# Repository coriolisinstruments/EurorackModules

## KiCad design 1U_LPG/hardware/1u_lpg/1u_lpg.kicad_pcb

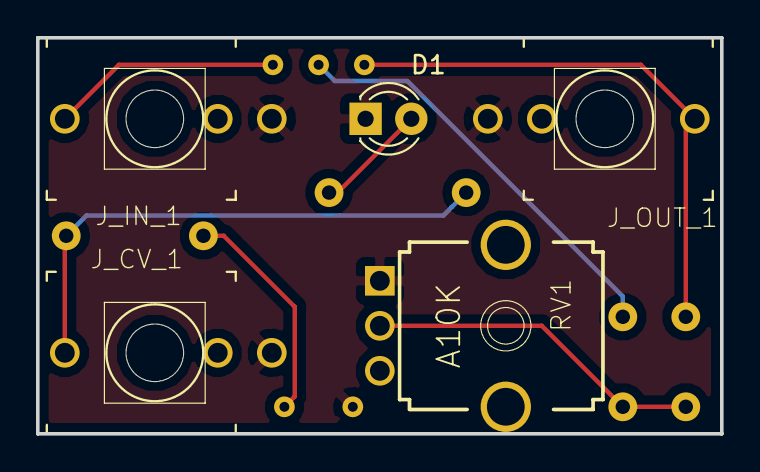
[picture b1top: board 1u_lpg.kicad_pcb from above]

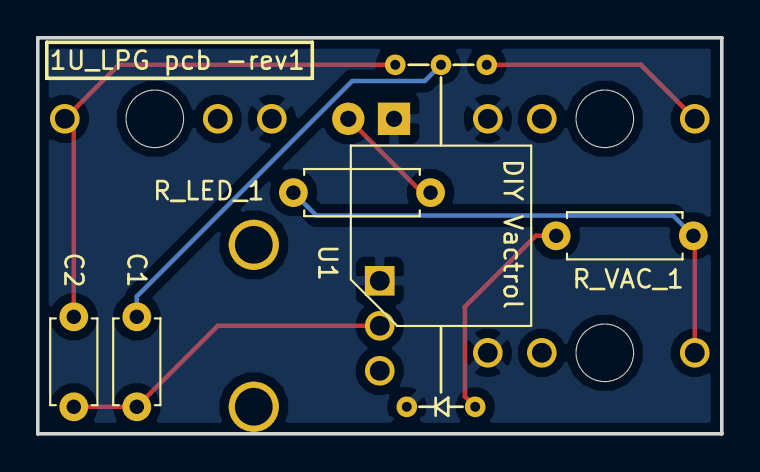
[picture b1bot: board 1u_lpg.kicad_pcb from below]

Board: 2 copper layers, 38.0 x 22.0 mm, 10 parts (5 on the bottom side), 8 nets.

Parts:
C1, C2: 0.1uF; C_Disc_D4.7mm_W2.5mm_P5.00mm
D1: LED; LED_D3.0mm
J_CV_1: thonkiconn; MusicThingModular-WQP-PJ301M-12_JACK
J_IN_1: thonkiconn; MusicThingModular-WQP-PJ301M-12_JACK
J_OUT_1: thonkiconn; MusicThingModular-WQP-PJ301M-12_JACK
RV1: A10K; MusicThingModular-9MM_SNAP-IN_POT
R_LED_1: 20K; R_Axial_DIN0207_L6.3mm_D2.5mm_P7.62mm_Horizontal
R_VAC_1: 100K; R_Axial_DIN0207_L6.3mm_D2.5mm_P7.62mm_Horizontal
U1: VTL5Cx2; DIY_Optoisolator_VTL5Cx2

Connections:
GND: D1.1, J_CV_1.P$3_SLEEVE, J_IN_1.P$3_SLEEVE, J_OUT_1.P$3_SLEEVE, RV1.1, U1.1
unnamed: C1.1, U1.4
unnamed: C1.2, C2.2, RV1.2
unnamed: C2.1, J_OUT_1.P$1_TIP, U1.3
unnamed: D1.2, R_LED_1.1
unnamed: J_CV_1.P$1_TIP, R_LED_1.2, R_VAC_1.2
unnamed: J_IN_1.P$1_TIP, U1.5
unnamed: R_VAC_1.1, U1.2

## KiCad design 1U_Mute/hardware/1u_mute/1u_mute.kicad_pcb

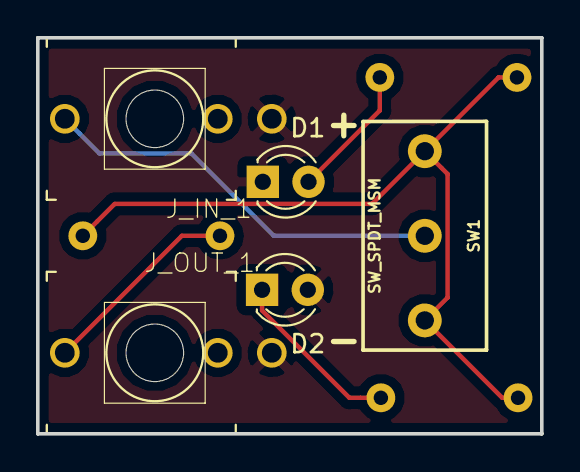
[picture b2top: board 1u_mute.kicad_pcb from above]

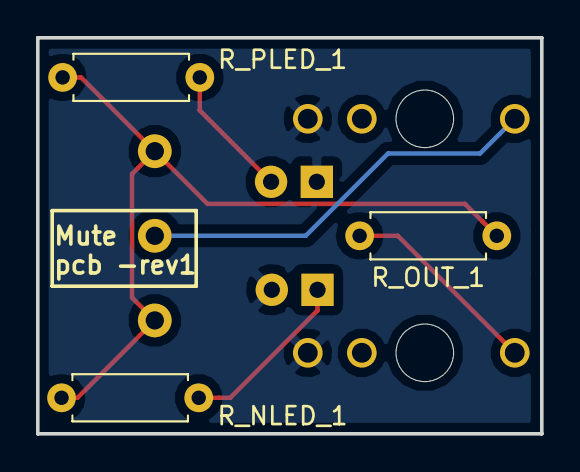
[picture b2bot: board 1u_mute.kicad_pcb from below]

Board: 2 copper layers, 28.0 x 22.0 mm, 8 parts (3 on the bottom side), 6 nets.

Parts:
D1: LED_POS; LED_D3.0mm
D2: LED_NEG; LED_D3.0mm
J_IN_1: thonkiconn; MusicThingModular-WQP-PJ301M-12_JACK
J_OUT_1: thonkiconn; MusicThingModular-WQP-PJ301M-12_JACK
R_NLED_1: 1K; R_Axial_DIN0207_L6.3mm_D2.5mm_P7.62mm_Horizontal
R_OUT_1: 1K; R_Axial_DIN0207_L6.3mm_D2.5mm_P7.62mm_Horizontal
R_PLED_1: 1K; R_Axial_DIN0207_L6.3mm_D2.5mm_P7.62mm_Horizontal
SW1: SW_SPDT_MSM; Miniswitch(4.7mm)

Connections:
GND: D1.1, D2.2, J_IN_1.P$3_SLEEVE, J_OUT_1.P$3_SLEEVE
unnamed: D1.2, R_PLED_1.1
unnamed: D2.1, R_NLED_1.1
unnamed: J_IN_1.P$1_TIP, SW1.2
unnamed: J_OUT_1.P$1_TIP, R_OUT_1.2
unnamed: R_NLED_1.2, R_OUT_1.1, R_PLED_1.2, SW1.1, SW1.3

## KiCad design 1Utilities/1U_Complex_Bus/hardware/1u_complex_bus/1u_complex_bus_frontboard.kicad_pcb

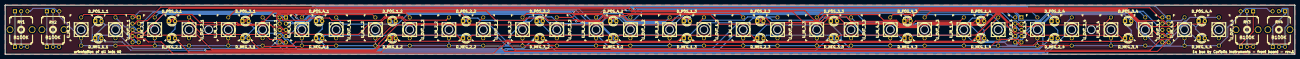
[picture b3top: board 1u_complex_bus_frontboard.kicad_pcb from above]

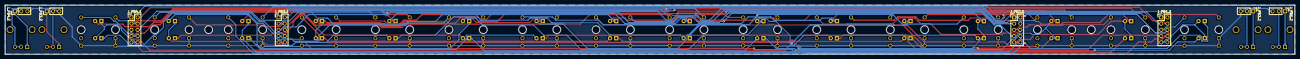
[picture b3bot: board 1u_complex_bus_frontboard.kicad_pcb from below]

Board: 2 copper layers, 526.0 x 20.0 mm, 78 parts (8 on the bottom side), 73 nets.

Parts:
D_NEG_1_1, D_NEG_1_2, D_NEG_1_3, D_NEG_1_4, D_NEG_2_1, D_NEG_2_2, D_NEG_2_3, D_NEG_2_4, D_NEG_3_1, D_NEG_3_2, D_NEG_3_3, D_NEG_3_4, D_NEG_4_1, D_NEG_4_2, D_NEG_4_3, D_NEG_4_4: LED; LED_D3.0mm
D_POS_1_1, D_POS_1_2, D_POS_1_3, D_POS_1_4, D_POS_2_1, D_POS_2_2, D_POS_2_3, D_POS_2_4, D_POS_3_1, D_POS_3_2, D_POS_3_3, D_POS_3_4, D_POS_4_1, D_POS_4_2, D_POS_4_3, D_POS_4_4: LED; LED_D3.0mm
H_FB_1, H_FB_2: MountingHole; MountingHole_3.2mm_M3
J_FB1.1, J_FB2.1, J_FB3.1, J_FB4.1: Conn_02x05_Odd_Even; PinHeader_2x05_P2.54mm_Vertical
J_FB1.2, J_FB2.2, J_FB3.2, J_FB4.2: Conn_01x03; PinHeader_1x03_P2.54mm_Vertical
RV1, RV2, RV3, RV4: B100K; 9MM_SNAP-IN_POT
U_IN_1_1, U_IN_1_2, U_IN_1_3, U_IN_1_4, U_IN_2_1, U_IN_2_2, U_IN_2_3, U_IN_2_4, U_IN_3_1, U_IN_3_2, U_IN_3_3, U_IN_3_4, U_IN_4_1, U_IN_4_2, U_IN_4_3, U_IN_4_4: THONKICONNNEW; MusicThingModular-WQP-PJ301M-12_JACK
U_OUT_1_1, U_OUT_1_2, U_OUT_1_3, U_OUT_1_4, U_OUT_2_1, U_OUT_2_2, U_OUT_2_3, U_OUT_2_4, U_OUT_3_1, U_OUT_3_2, U_OUT_3_3, U_OUT_3_4, U_OUT_4_1, U_OUT_4_2, U_OUT_4_3, U_OUT_4_4: THONKICONNNEW; MusicThingModular-WQP-PJ301M-12_JACK

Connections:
/cv_bus1/FB_IN_1_1: J_FB1.1.1, U_IN_1_1.P$1_TIP
/cv_bus1/FB_IN_1_2: J_FB1.1.2, U_IN_1_2.P$1_TIP
/cv_bus1/FB_IN_1_3: J_FB1.1.3, U_IN_1_3.P$1_TIP
/cv_bus1/FB_IN_1_4: J_FB1.1.4, U_IN_1_4.P$1_TIP
/cv_bus1/FB_LEDS_IN_1: D_NEG_1_1.1, D_POS_1_1.2, J_FB1.1.9
/cv_bus1/FB_LEDS_OUT_1: D_NEG_1_4.2, D_POS_1_4.1, J_FB1.1.10
/cv_bus1/FB_OUT_1_1: J_FB1.1.5, U_OUT_1_1.P$1_TIP
/cv_bus1/FB_OUT_1_2: J_FB1.1.6, U_OUT_1_2.P$1_TIP
/cv_bus1/FB_OUT_1_3: J_FB1.1.7, U_OUT_1_3.P$1_TIP
/cv_bus1/FB_OUT_1_4: J_FB1.1.8, U_OUT_1_4.P$1_TIP
/cv_bus1/FB_POT_1: J_FB1.2.1, RV1.1
/cv_bus1/FB_POT_2: J_FB1.2.2, RV1.2, RV1.3
/cv_bus2/FB_IN_2_1: J_FB2.1.1, U_IN_2_1.P$1_TIP
/cv_bus2/FB_IN_2_2: J_FB2.1.2, U_IN_2_2.P$1_TIP
/cv_bus2/FB_IN_2_3: J_FB2.1.3, U_IN_2_3.P$1_TIP
/cv_bus2/FB_IN_2_4: J_FB2.1.4, U_IN_2_4.P$1_TIP
/cv_bus2/FB_LEDS_IN_2: D_NEG_2_1.1, D_POS_2_1.2, J_FB2.1.9
/cv_bus2/FB_LEDS_OUT_2: D_NEG_2_4.2, D_POS_2_4.1, J_FB2.1.10
/cv_bus2/FB_OUT_2_1: J_FB2.1.5, U_OUT_2_1.P$1_TIP
/cv_bus2/FB_OUT_2_2: J_FB2.1.6, U_OUT_2_2.P$1_TIP
/cv_bus2/FB_OUT_2_3: J_FB2.1.7, U_OUT_2_3.P$1_TIP
/cv_bus2/FB_OUT_2_4: J_FB2.1.8, U_OUT_2_4.P$1_TIP
/cv_bus2/FB_POT_1: J_FB2.2.1, RV2.1
/cv_bus2/FB_POT_2: J_FB2.2.2, RV2.2, RV2.3
/cv_bus3/FB_IN_3_1: J_FB3.1.1, U_IN_3_1.P$1_TIP
/cv_bus3/FB_IN_3_2: J_FB3.1.2, U_IN_3_2.P$1_TIP
/cv_bus3/FB_IN_3_3: J_FB3.1.3, U_IN_3_3.P$1_TIP
/cv_bus3/FB_IN_3_4: J_FB3.1.4, U_IN_3_4.P$1_TIP
/cv_bus3/FB_LEDS_IN_3: D_NEG_3_1.1, D_POS_3_1.2, J_FB3.1.9
/cv_bus3/FB_LEDS_OUT_3: D_NEG_3_4.2, D_POS_3_4.1, J_FB3.1.10
/cv_bus3/FB_OUT_3_1: J_FB3.1.5, U_OUT_3_1.P$1_TIP
/cv_bus3/FB_OUT_3_2: J_FB3.1.6, U_OUT_3_2.P$1_TIP
/cv_bus3/FB_OUT_3_3: J_FB3.1.7, U_OUT_3_3.P$1_TIP
/cv_bus3/FB_OUT_3_4: J_FB3.1.8, U_OUT_3_4.P$1_TIP
/cv_bus3/FB_POT_1: J_FB3.2.1, RV3.1
/cv_bus3/FB_POT_2: J_FB3.2.2, RV3.2, RV3.3
/cv_bus4/FB_IN_4_1: J_FB4.1.1, U_IN_4_1.P$1_TIP
/cv_bus4/FB_IN_4_2: J_FB4.1.2, U_IN_4_2.P$1_TIP
/cv_bus4/FB_IN_4_3: J_FB4.1.3, U_IN_4_3.P$1_TIP
/cv_bus4/FB_IN_4_4: J_FB4.1.4, U_IN_4_4.P$1_TIP
/cv_bus4/FB_LEDS_IN_4: D_NEG_4_1.1, D_POS_4_1.2, J_FB4.1.9
/cv_bus4/FB_LEDS_OUT_4: D_NEG_4_4.2, D_POS_4_4.1, J_FB4.1.10
/cv_bus4/FB_OUT_4_1: J_FB4.1.5, U_OUT_4_1.P$1_TIP
/cv_bus4/FB_OUT_4_2: J_FB4.1.6, U_OUT_4_2.P$1_TIP
/cv_bus4/FB_OUT_4_3: J_FB4.1.7, U_OUT_4_3.P$1_TIP
/cv_bus4/FB_OUT_4_4: J_FB4.1.8, U_OUT_4_4.P$1_TIP
/cv_bus4/FB_POT_1: J_FB4.2.1, RV4.1
/cv_bus4/FB_POT_2: J_FB4.2.2, RV4.2, RV4.3
FB_GND: J_FB1.2.3, J_FB2.2.3, J_FB3.2.3, J_FB4.2.3, U_IN_1_1.P$2_SWITCH, U_IN_1_1.P$3_SLEEVE, U_IN_1_2.P$2_SWITCH, U_IN_1_2.P$3_SLEEVE, U_IN_1_3.P$2_SWITCH, U_IN_1_3.P$3_SLEEVE, U_IN_1_4.P$2_SWITCH, U_IN_1_4.P$3_SLEEVE, U_IN_2_1.P$2_SWITCH, U_IN_2_1.P$3_SLEEVE, U_IN_2_2.P$2_SWITCH, U_IN_2_2.P$3_SLEEVE, U_IN_2_3.P$2_SWITCH, U_IN_2_3.P$3_SLEEVE, U_IN_2_4.P$2_SWITCH, U_IN_2_4.P$3_SLEEVE, U_IN_3_1.P$2_SWITCH, U_IN_3_1.P$3_SLEEVE, U_IN_3_2.P$2_SWITCH, U_IN_3_2.P$3_SLEEVE, U_IN_3_3.P$2_SWITCH, U_IN_3_3.P$3_SLEEVE, U_IN_3_4.P$2_SWITCH, U_IN_3_4.P$3_SLEEVE, U_IN_4_1.P$2_SWITCH, U_IN_4_1.P$3_SLEEVE, U_IN_4_2.P$2_SWITCH, U_IN_4_2.P$3_SLEEVE, U_IN_4_3.P$2_SWITCH, U_IN_4_3.P$3_SLEEVE, U_IN_4_4.P$2_SWITCH, U_IN_4_4.P$3_SLEEVE, U_OUT_1_1.P$3_SLEEVE, U_OUT_1_2.P$3_SLEEVE, U_OUT_1_3.P$3_SLEEVE, U_OUT_1_4.P$3_SLEEVE, U_OUT_2_1.P$3_SLEEVE, U_OUT_2_2.P$3_SLEEVE, U_OUT_2_3.P$3_SLEEVE, U_OUT_2_4.P$3_SLEEVE, U_OUT_3_1.P$3_SLEEVE, U_OUT_3_2.P$3_SLEEVE, U_OUT_3_3.P$3_SLEEVE, U_OUT_3_4.P$3_SLEEVE, U_OUT_4_1.P$3_SLEEVE, U_OUT_4_2.P$3_SLEEVE, U_OUT_4_3.P$3_SLEEVE, U_OUT_4_4.P$3_SLEEVE
unnamed: D_NEG_1_1.2, D_NEG_1_2.1
unnamed: D_NEG_1_2.2, D_NEG_1_3.1
unnamed: D_NEG_1_3.2, D_NEG_1_4.1
unnamed: D_NEG_2_1.2, D_NEG_2_2.1
unnamed: D_NEG_2_2.2, D_NEG_2_3.1
unnamed: D_NEG_2_3.2, D_NEG_2_4.1
unnamed: D_NEG_3_1.2, D_NEG_3_2.1
unnamed: D_NEG_3_2.2, D_NEG_3_3.1
unnamed: D_NEG_3_3.2, D_NEG_3_4.1
unnamed: D_NEG_4_1.2, D_NEG_4_2.1
unnamed: D_NEG_4_2.2, D_NEG_4_3.1
unnamed: D_NEG_4_3.2, D_NEG_4_4.1
unnamed: D_POS_1_1.1, D_POS_1_2.2
unnamed: D_POS_1_2.1, D_POS_1_3.2
unnamed: D_POS_1_3.1, D_POS_1_4.2
unnamed: D_POS_2_1.1, D_POS_2_2.2
unnamed: D_POS_2_2.1, D_POS_2_3.2
unnamed: D_POS_2_3.1, D_POS_2_4.2
unnamed: D_POS_3_1.1, D_POS_3_2.2
unnamed: D_POS_3_2.1, D_POS_3_3.2
unnamed: D_POS_3_3.1, D_POS_3_4.2
unnamed: D_POS_4_1.1, D_POS_4_2.2
unnamed: D_POS_4_2.1, D_POS_4_3.2
unnamed: D_POS_4_3.1, D_POS_4_4.2

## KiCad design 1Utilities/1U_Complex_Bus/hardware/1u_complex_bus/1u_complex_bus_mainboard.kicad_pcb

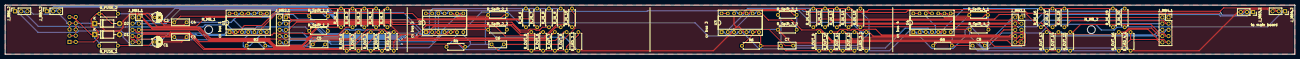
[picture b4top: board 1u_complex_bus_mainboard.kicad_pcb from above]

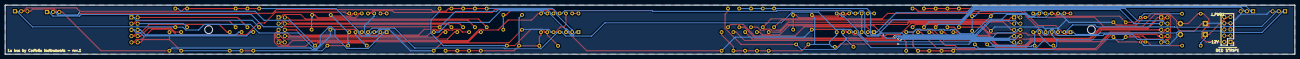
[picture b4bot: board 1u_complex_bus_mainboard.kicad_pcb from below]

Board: 2 copper layers, 526.0 x 20.0 mm, 80 parts (2 on the bottom side), 66 nets.

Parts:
C1, C2: 10uF (25V); CP_Radial_D4.0mm_P2.00mm
C3, C4: 100nF; C_Disc_D7.0mm_W2.5mm_P5.00mm
C5, C6, C7, C8: 10pF; C_Disc_D7.0mm_W2.5mm_P5.00mm
D1, D2: IN4001; D_DO-41_SOD81_P10.16mm_Horizontal
H_MB_1, H_MB_2: MountingHole; MountingHole_3.2mm_M3
J_MB1.1, J_MB2.1, J_MB3.1, J_MB4.1: Conn_02x05_Odd_Even; PinSocket_2x05_P2.54mm_Vertical
J_MB1.2, J_MB2.2, J_MB3.2, J_MB4.2: Conn_01x03; PinSocket_1x03_P2.54mm_Vertical
J_PWR1: Conn_02x05_Odd_Even; PinHeader_2x05_P2.54mm_Vertical
MK1: CoriolisLogo; art_Coriolis_logo_copper
R2, R4, R6, R8: 100K; R_Axial_DIN0207_L6.3mm_D2.5mm_P7.62mm_Horizontal
R_FUSE_1, R_FUSE_2: 10R; R_Axial_DIN0207_L6.3mm_D2.5mm_P7.62mm_Horizontal
R_IN_1, R_IN_2, R_IN_3, R_IN_4, R_IN_5, R_IN_6, R_IN_7, R_IN_8, R_IN_9, R_IN_10, R_IN_11, R_IN_12, R_IN_13, R_IN_14, R_IN_15, R_IN_16, R_IN_17, R_IN_18, R_IN_19, R_IN_20: 100K; R_Axial_DIN0207_L6.3mm_D2.5mm_P7.62mm_Horizontal
R_LED_1_1: 1K; R_Axial_DIN0207_L6.3mm_D2.5mm_P7.62mm_Horizontal
R_LED_2_1: 470R; R_Axial_DIN0207_L6.3mm_D2.5mm_P7.62mm_Horizontal
R_LED_3_1, R_LED_4_1: 5K1; R_Axial_DIN0207_L6.3mm_D2.5mm_P7.62mm_Horizontal
R_OUT_1, R_OUT_2, R_OUT_3, R_OUT_4, R_OUT_5, R_OUT_6, R_OUT_7, R_OUT_8, R_OUT_9, R_OUT_10, R_OUT_11, R_OUT_12, R_OUT_13, R_OUT_14, R_OUT_15, R_OUT_16: 51; R_Axial_DIN0207_L6.3mm_D2.5mm_P7.62mm_Horizontal
R_Split_1_1, R_Split_2_1, R_Split_3_1, R_Split_4_1: 10K; R_Axial_DIN0207_L6.3mm_D2.5mm_P7.62mm_Horizontal
R_Split_1_2, R_Split_2_2, R_Split_3_2, R_Split_4_2: 1K; R_Axial_DIN0207_L6.3mm_D2.5mm_P7.62mm_Horizontal
U1, U2, U3, U4: TL074; DIP-14_W7.62mm_Socket

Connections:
+12V: C1.1, C3.1, R_FUSE_1.1, U1.4, U2.4, U3.4, U4.4
-12V: C2.2, C4.2, R_FUSE_2.1, U1.11, U2.11, U3.11, U4.11
/cv_bus1/IN_1_1: J_MB1.1.1, R_IN_1.1
/cv_bus1/IN_1_2: J_MB1.1.2, R_IN_2.1
/cv_bus1/IN_1_3: J_MB1.1.3, R_IN_3.1
/cv_bus1/IN_1_4: J_MB1.1.4, R_IN_4.1
/cv_bus1/LEDS_IN_1: J_MB1.1.9, U1.8
/cv_bus1/LEDS_OUT_1: C5.1, J_MB1.1.10, R2.2, R_LED_1_1.2, R_OUT_1.1, R_OUT_2.1, R_OUT_3.1, R_OUT_4.1, R_Split_1_1.1, U1.7, U1.9
/cv_bus1/OUT_1_1: J_MB1.1.5, R_OUT_1.2
/cv_bus1/OUT_1_2: J_MB1.1.6, R_OUT_2.2
/cv_bus1/OUT_1_3: J_MB1.1.7, R_OUT_3.2
/cv_bus1/OUT_1_4: J_MB1.1.8, R_OUT_4.2
/cv_bus1/POT_1: J_MB1.2.1, R_IN_5.1, U1.1
/cv_bus1/POT_2: J_MB1.2.2, R_IN_1.2, R_IN_2.2, R_IN_3.2, R_IN_4.2, U1.2
/cv_bus2/IN_2_1: J_MB2.1.1, R_IN_6.1
/cv_bus2/IN_2_2: J_MB2.1.2, R_IN_7.1
/cv_bus2/IN_2_3: J_MB2.1.3, R_IN_8.1
/cv_bus2/IN_2_4: J_MB2.1.4, R_IN_9.1
/cv_bus2/LEDS_IN_2: J_MB2.1.9, U2.8
/cv_bus2/LEDS_OUT_2: C6.1, J_MB2.1.10, R4.2, R_LED_2_1.2, R_OUT_5.1, R_OUT_6.1, R_OUT_7.1, R_OUT_8.1, R_Split_2_1.1, U2.7, U2.9
/cv_bus2/OUT_2_1: J_MB2.1.5, R_OUT_5.2
/cv_bus2/OUT_2_2: J_MB2.1.6, R_OUT_6.2
/cv_bus2/OUT_2_3: J_MB2.1.7, R_OUT_7.2
/cv_bus2/OUT_2_4: J_MB2.1.8, R_OUT_8.2
/cv_bus2/POT_1: J_MB2.2.1, R_IN_10.1, U2.1
/cv_bus2/POT_2: J_MB2.2.2, R_IN_6.2, R_IN_7.2, R_IN_8.2, R_IN_9.2, U2.2
/cv_bus3/IN_3_1: J_MB3.1.1, R_IN_11.1
/cv_bus3/IN_3_2: J_MB3.1.2, R_IN_12.1
/cv_bus3/IN_3_3: J_MB3.1.3, R_IN_13.1
/cv_bus3/IN_3_4: J_MB3.1.4, R_IN_14.1
/cv_bus3/LEDS_IN_3: J_MB3.1.9, U3.8
/cv_bus3/LEDS_OUT_3: J_MB3.1.10, R_LED_3_1.2, U3.9
/cv_bus3/OUT_3_1: J_MB3.1.5, R_OUT_9.2
/cv_bus3/OUT_3_2: J_MB3.1.6, R_OUT_10.2
/cv_bus3/OUT_3_3: J_MB3.1.7, R_OUT_11.2
/cv_bus3/OUT_3_4: J_MB3.1.8, R_OUT_12.2
/cv_bus3/POT_1: J_MB3.2.1, R_IN_15.1, U3.1
/cv_bus3/POT_2: J_MB3.2.2, R_IN_11.2, R_IN_12.2, R_IN_13.2, R_IN_14.2, U3.2
/cv_bus4/IN_4_1: J_MB4.1.1, R_IN_16.1
/cv_bus4/IN_4_2: J_MB4.1.2, R_IN_17.1
/cv_bus4/IN_4_3: J_MB4.1.3, R_IN_18.1
/cv_bus4/IN_4_4: J_MB4.1.4, R_IN_19.1
/cv_bus4/LEDS_IN_4: J_MB4.1.9, U4.8
/cv_bus4/LEDS_OUT_4: C8.1, J_MB4.1.10, R8.2, R_LED_4_1.2, R_OUT_13.1, R_OUT_14.1, R_OUT_15.1, R_OUT_16.1, R_Split_4_1.1, U4.7, U4.9
/cv_bus4/OUT_4_1: J_MB4.1.5, R_OUT_13.2
/cv_bus4/OUT_4_2: J_MB4.1.6, R_OUT_14.2
/cv_bus4/OUT_4_3: J_MB4.1.7, R_OUT_15.2
/cv_bus4/OUT_4_4: J_MB4.1.8, R_OUT_16.2
/cv_bus4/POT_1: J_MB4.2.1, R_IN_20.1, U4.1
/cv_bus4/POT_2: J_MB4.2.2, R_IN_16.2, R_IN_17.2, R_IN_18.2, R_IN_19.2, U4.2
GND: C1.2, C2.1, C3.2, C4.1, D1.2, D2.1, J_MB1.2.3, J_MB2.2.3, J_MB3.2.3, J_MB4.2.3, J_PWR1.3, J_PWR1.4, J_PWR1.5, J_PWR1.6, J_PWR1.7, J_PWR1.8, R_LED_1_1.1, R_LED_2_1.1, R_LED_3_1.1, R_LED_4_1.1, R_Split_1_2.1, R_Split_2_2.1, R_Split_3_2.1, R_Split_4_2.1, U1.3, U1.5, U1.12, U2.3, U2.5, U2.12, U3.3, U3.5, U3.12, U4.3, U4.5, U4.12
unnamed: C5.2, R2.1, R_IN_5.2, U1.6
unnamed: C6.2, R4.1, R_IN_10.2, U2.6
unnamed: C7.1, R6.2, R_OUT_9.1, R_OUT_10.1, R_OUT_11.1, R_OUT_12.1, R_Split_3_1.1, U3.7
unnamed: C7.2, R6.1, R_IN_15.2, U3.6
unnamed: C8.2, R8.1, R_IN_20.2, U4.6
unnamed: D1.1, J_PWR1.9, J_PWR1.10, R_FUSE_1.2
unnamed: D2.2, J_PWR1.1, J_PWR1.2, R_FUSE_2.2
unnamed: R_Split_1_1.2, R_Split_1_2.2, U1.10
unnamed: R_Split_2_1.2, R_Split_2_2.2, U2.10
unnamed: R_Split_3_1.2, R_Split_3_2.2, U3.10
unnamed: R_Split_4_1.2, R_Split_4_2.2, U4.10
unnamed: U1.13, U1.14
unnamed: U2.13, U2.14
unnamed: U3.13, U3.14
unnamed: U4.13, U4.14

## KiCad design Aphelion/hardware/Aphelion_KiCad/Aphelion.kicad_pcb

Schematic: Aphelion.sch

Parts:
C1, C4, C5, C12, C17, C18: 10uF; CP_Radial_D5.0mm_P2.50mm
C2, C6, C9, C16: 220nF; C_Rect_L7.0mm_W2.5mm_P5.00mm
C3, C15, C19, C20, C21, C22: 47nF; C_Rect_L7.0mm_W2.5mm_P5.00mm
C7, C8: 100nF; C_Rect_L7.0mm_W2.5mm_P5.00mm
C10: 1uF; C_Rect_L7.0mm_W2.5mm_P5.00mm
C11, C23, C24: 33uF; CP_Radial_D5.0mm_P2.50mm
C13, C14: 22nF; C_Rect_L7.0mm_W2.5mm_P5.00mm
D1, D2: 1N4001; D_DO-41_SOD81_P10.16mm_Horizontal
F1, F2: Polyfuse; Fuse_TE5_Littlefuse-395Series
J1: Conn_02x05_Odd_Even; Pin_Header_Straight_2x05_Pitch2.54mm
J2: Conn_01x08_Male; Pin_Header_Straight_1x08_Pitch2.54mm
J3, J4: Conn_01x06_Male; Pin_Header_Straight_1x06_Pitch2.54mm
J5: Conn_01x08_Female; Pin_Header_Straight_1x08_Pitch2.54mm
J6, J7: Conn_01x06_Female; Pin_Header_Straight_1x06_Pitch2.54mm
J_IN1: Audio-Jack-2_Switch; WQP-PJ301M-12_JACK
J_OUT1: Audio-Jack-2_Switch; WQP-PJ301M-12_JACK
Q1, Q2, Q3, Q4: BC547; TO-92_Molded_Narrow
R1, R2, R5, R6, R7, R10, R17: 47K; R_Axial_DIN0207_L6.3mm_D2.5mm_P7.62mm_Horizontal
R3, R11, R12, R15, R16, R18, R19, R23, R25: 10K; R_Axial_DIN0207_L6.3mm_D2.5mm_P7.62mm_Horizontal
R4, R26, R27: 1M; R_Axial_DIN0207_L6.3mm_D2.5mm_P7.62mm_Horizontal
R8, R9, R30, R31, R32, R33: 100K; R_Axial_DIN0207_L6.3mm_D2.5mm_P7.62mm_Horizontal
R13: 470r; R_Axial_DIN0207_L6.3mm_D2.5mm_P7.62mm_Horizontal
R14: 20K; R_Axial_DIN0207_L6.3mm_D2.5mm_P7.62mm_Horizontal
R20, R21: 5K6; R_Axial_DIN0207_L6.3mm_D2.5mm_P7.62mm_Horizontal
R22, R24: 22K; R_Axial_DIN0207_L6.3mm_D2.5mm_P7.62mm_Horizontal
R28, R29: 3M9; R_Axial_DIN0207_L6.3mm_D2.5mm_P7.62mm_Horizontal
R34, R35: 4K7; R_Axial_DIN0207_L6.3mm_D2.5mm_P7.62mm_Horizontal
R36, R37, R38, R39: 220K; R_Axial_DIN0207_L6.3mm_D2.5mm_P7.62mm_Horizontal
RV_COMP_H1: A500K; 9MM_SNAP-IN_POT
RV_COMP_L1: A500K; 9MM_SNAP-IN_POT
RV_LVL_H1: A100K; 9MM_SNAP-IN_POT
RV_LVL_L1: A100K; 9MM_SNAP-IN_POT
RV_XOVER_F1: A100K; DUAL_9MM_SNAP-IN_POT
U1: TL072; DIP-8_W7.62mm_Socket
U2, U3: TL074; DIP-14_W7.62mm_Socket
U4, U5: NSL-32; Optoisolator_NSL-32

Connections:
/+6V: C11.1, J5.2, R7.1, R8.2, R9.1, R14.1, R16.1, R18.1, R26.1, R27.1, U1.3 (+), U2.10 (+), U2.12 (+), U3.10 (+), U3.12 (+)
/+6V_FB: J2.2, R4.1, RV_LVL_H1.3, RV_LVL_L1.3
/+12V: C4.1, C7.1, F1.1, R8.1, R34.2, R35.2, U1.8 (V+), U2.4 (V+), U3.4 (V+)
/-12V: C5.2, C8.2, F2.2, U1.4 (V-), U2.11 (V-), U3.11 (V-)
/A_IN: J5.3, U2.3 (+)
/A_IN_FB: J2.3, R3.1, R4.2
/A_OUT: J5.4, R10.1, U1.7
/A_OUT_FB: J2.4, R13.2
/COMP_H_OUT: C3.2, C21.2, R32.1, U3.8
/COMP_L_OUT: C1.1, C22.2, R33.1, U3.14
/GND: C4.2, C5.1, C7.2, C8.1, C11.2, C15.2, C16.2, C23.2, C24.2, D1.2 (A), D2.1 (K), J1.3, J1.4, J1.5, J1.6, J1.7, J1.8, J5.1, Q1.3 (E), Q2.3 (E), Q3.3 (E), Q4.3 (E), R9.2, R36.2, R37.2, R38.1, R39.1
/GND_FB: J2.1, J_IN1.2, J_OUT1.2, R17.1
/RV_COMP_H_1: C15.1, J6.1, J6.2
/RV_COMP_H_1_FB: J3.1, RV_COMP_H1.1
/RV_COMP_H_2_FB: J3.2, RV_COMP_H1.2
/RV_COMP_H_3: J6.3, R22.2
/RV_COMP_H_3_FB: J3.3, RV_COMP_H1.3
/RV_COMP_L_1: C16.1, J6.4, J6.5
/RV_COMP_L_1_FB: J3.4, RV_COMP_L1.1
/RV_COMP_L_2_FB: J3.5, RV_COMP_L1.2
/RV_COMP_L_3: J6.6, R24.2
/RV_COMP_L_3_FB: J3.6, RV_COMP_L1.3
/RV_LVL_H_1: C3.1, J5.7
/RV_LVL_H_1_FB: J2.7, RV_LVL_H1.1
/RV_LVL_H_2: C9.2, J5.8
/RV_LVL_H_2_FB: J2.8, RV_LVL_H1.2
/RV_LVL_L_1: C1.2, J5.5
/RV_LVL_L_1_FB: J2.5, RV_LVL_L1.1
/RV_LVL_L_2: C2.2, J5.6
/RV_LVL_L_2_FB: J2.6, RV_LVL_L1.2
/RV_XOVER_1: C17.1, J7.1, R15.1, U2.7
/RV_XOVER_1_FB: J4.1, RV_XOVER_F1.1
/RV_XOVER_2: J7.2, R20.2
/RV_XOVER_2_FB: J4.2, RV_XOVER_F1.2
/RV_XOVER_3: J7.3, R16.2
/RV_XOVER_3_FB: J4.3, RV_XOVER_F1.3
/RV_XOVER_4: C13.1, J7.4, R14.2, U2.5 (+), U2.8
/RV_XOVER_4_FB: J4.4, RV_XOVER_F1.4
/RV_XOVER_5: J7.5, R21.2
/RV_XOVER_5_FB: J4.5, RV_XOVER_F1.5
/RV_XOVER_6: J7.6, R18.2
/RV_XOVER_6_FB: J4.6, RV_XOVER_F1.6
/X_OVER_L_OUT: C14.1, C18.1, R19.2, U2.14
unnamed: C2.1, R1.2
unnamed: C6.1, R3.2
unnamed: C6.2, J_IN1.1
unnamed: C9.1, R5.2
unnamed: C10.1, R11.2
unnamed: C10.2, U2.1, U2.2 (-)
unnamed: C12.1, R13.1
unnamed: C12.2, J_OUT1.1, R17.2
unnamed: C13.2, R20.1, U2.9 (-)
unnamed: C14.2, R21.1, U2.13 (-)
unnamed: C17.2, R23.2
unnamed: C18.2, R25.2
unnamed: C19.1, Q1.2 (B), R36.1
unnamed: C19.2, R28.1, R30.2, U3.1, U4.4 (R)
unnamed: C20.1, Q2.2 (B), R37.1
unnamed: C20.2, R29.1, R31.2, U3.7, U5.4 (R)
unnamed: C21.1, Q3.2 (B), R38.2
unnamed: C22.1, Q4.2 (B), R39.2
unnamed: C23.1, Q1.1 (C), Q3.1 (C), U4.2 (K)
unnamed: C24.1, Q2.1 (C), Q4.1 (C), U5.2 (K)
unnamed: D1.1 (K), F1.2, J1.9, J1.10
unnamed: D2.2 (A), F2.1, J1.1, J1.2
unnamed: R1.1, R2.2, U1.2 (-)
unnamed: R2.1, R6.2, U1.1
unnamed: R5.1, R7.2, U1.5 (+)
unnamed: R6.1, R10.2, U1.6 (-)
unnamed: R11.1, R12.2
unnamed: R12.1, R15.2, R19.1, U2.6 (-)
unnamed: R22.1, R28.2, U3.2 (-), U4.3 (R)
unnamed: R23.1, R26.2, U3.3 (+)
unnamed: R24.1, R29.2, U3.6 (-), U5.3 (R)
unnamed: R25.1, R27.2, U3.5 (+)
unnamed: R30.1, R32.2, U3.9 (-)
unnamed: R31.1, R33.2, U3.13 (-)
unnamed: R34.1, U4.1 (A)
unnamed: R35.1, U5.1 (A)

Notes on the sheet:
Input from busboard
Voltage divider
Input and cross-over
Output
High Compressor
Low Compressor
Front board

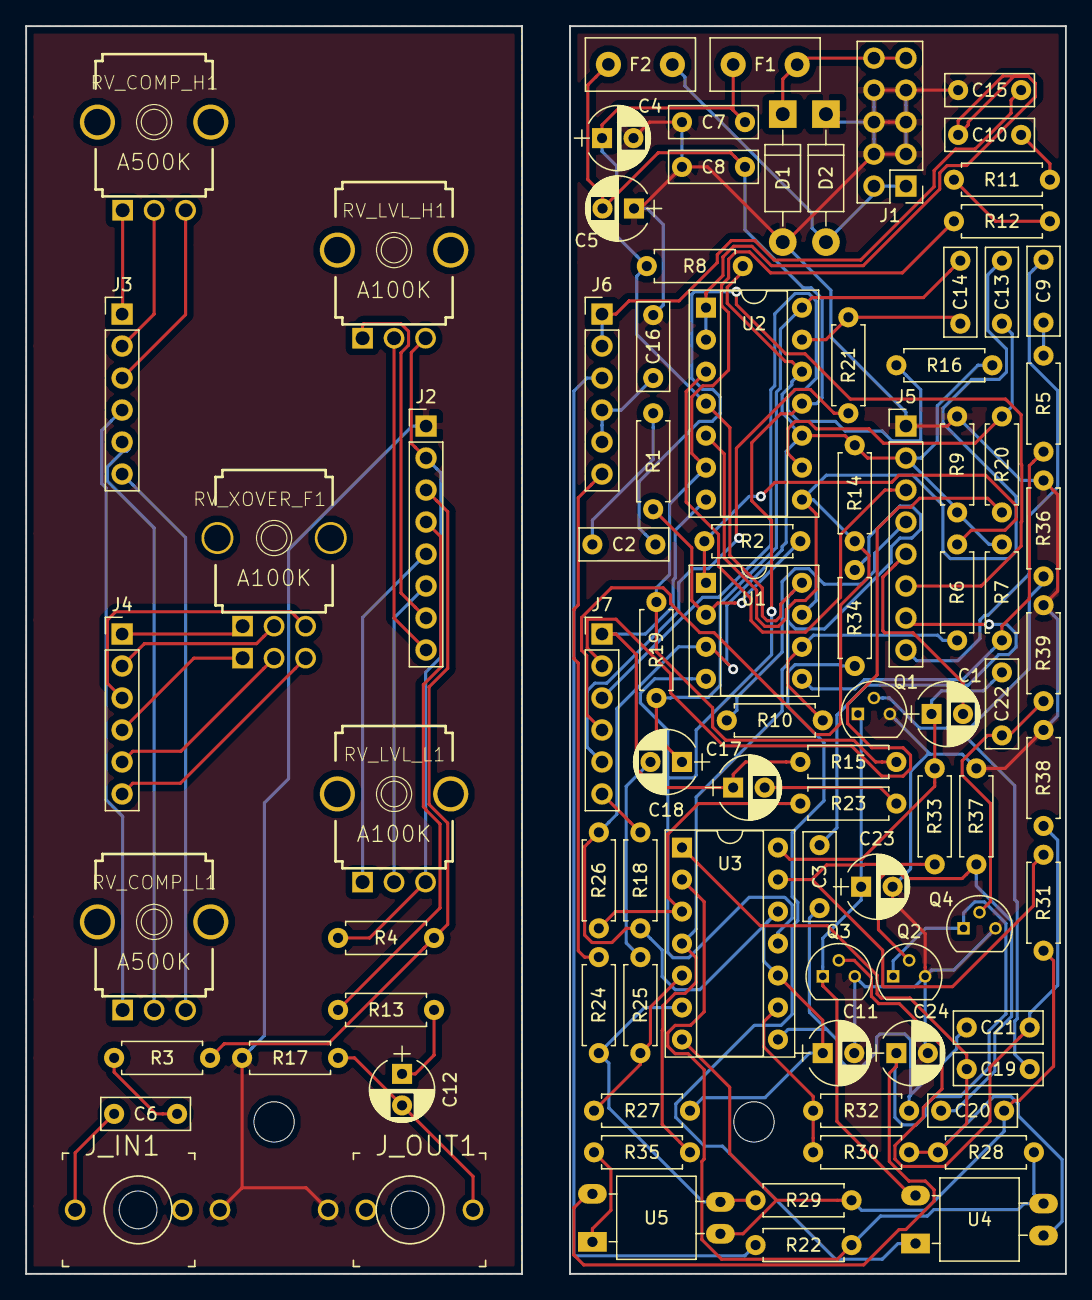
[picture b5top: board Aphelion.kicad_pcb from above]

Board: 2 copper layers, 39.4 x 99.1 mm, 90 parts (0 on the bottom side), 79 nets.

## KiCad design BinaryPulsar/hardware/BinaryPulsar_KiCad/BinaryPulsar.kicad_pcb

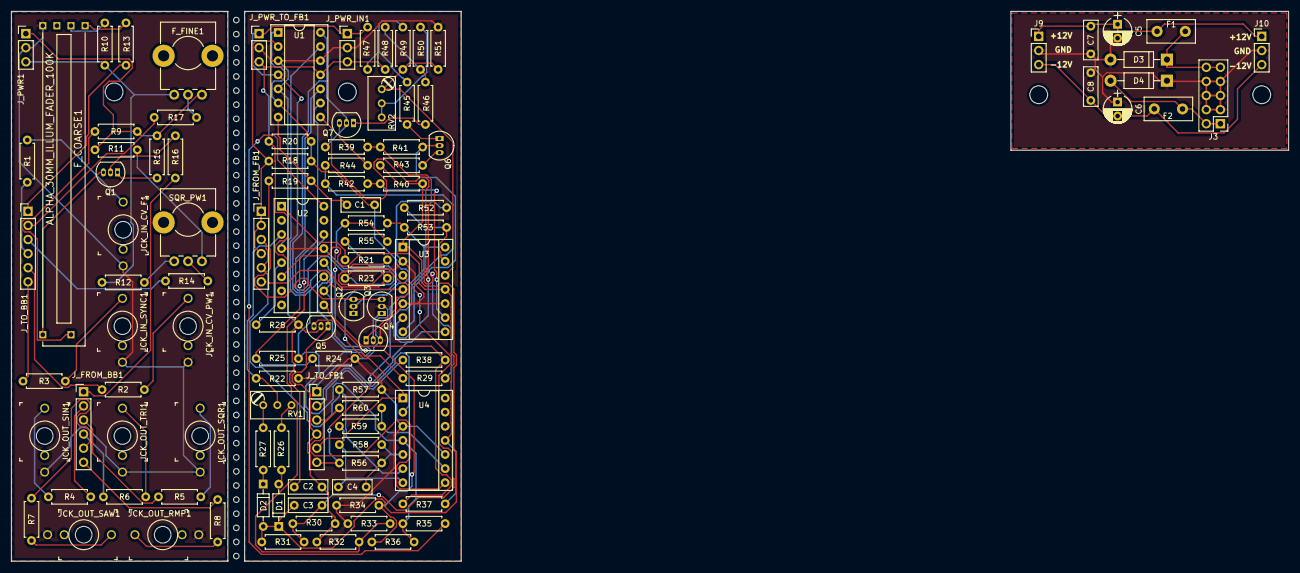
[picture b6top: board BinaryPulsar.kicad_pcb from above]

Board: 2 copper layers, 230.0 x 99.0 mm, 112 parts (0 on the bottom side), 88 nets.

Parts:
C1: 100pF; C_Rect_L7.0mm_W2.5mm_P5.00mm
C2: 0.02uF; C_Rect_L7.0mm_W2.5mm_P5.00mm
C3, C4: 10pF; C_Rect_L7.0mm_W2.5mm_P5.00mm
C5, C6: 10uF; CP_Radial_D5.0mm_P2.50mm
C7, C8: 100nF; C_Rect_L7.0mm_W2.5mm_P5.00mm
D1, D2: 1N4148; D_DO-35_SOD27_P7.62mm_Horizontal
D3, D4: 1N4001; D_DO-41_SOD81_P10.16mm_Horizontal
F1, F2: Polyfuse; Fuse_TE5_Littlefuse-395Series
F_COARSE1: ALPHA_30MM_ILLUM_FADER_100K; ALPHA_ILL_FADER_45MM
F_FINE1: 100K; Potentiometer_Alps_RK09K_Horizontal
J3: Conn_02x05_Odd_Even; Pin_Header_Straight_2x05_Pitch2.54mm
J9, J10: Conn_01x03_Male; Pin_Header_Straight_1x03_Pitch2.54mm
JCK_IN_CV_F1: THONKICONNNEW; WQP-PJ301M-12_JACK
JCK_IN_CV_PW1: THONKICONNNEW; WQP-PJ301M-12_JACK
JCK_IN_SYNC1: THONKICONNNEW; WQP-PJ301M-12_JACK
JCK_OUT_RMP1: THONKICONNNEW; WQP-PJ301M-12_JACK
JCK_OUT_SAW1: THONKICONNNEW; WQP-PJ301M-12_JACK
JCK_OUT_SIN1: THONKICONNNEW; WQP-PJ301M-12_JACK
JCK_OUT_SQR1: THONKICONNNEW; WQP-PJ301M-12_JACK
JCK_OUT_TRI1: THONKICONNNEW; WQP-PJ301M-12_JACK
J_FROM_BB1: Conn_01x06_Male; Pin_Header_Straight_1x06_Pitch2.54mm
J_FROM_FB1: Conn_01x06_Female; Pin_Header_Straight_1x06_Pitch2.54mm
J_PWR1: Conn_01x03_Male; Pin_Header_Straight_1x03_Pitch2.54mm
J_PWR_IN1: Conn_01x03_Male; Pin_Header_Straight_1x03_Pitch2.54mm
J_PWR_TO_FB1: Conn_01x03_Female; Pin_Header_Straight_1x03_Pitch2.54mm
J_TO_BB1: Conn_01x06_Male; Pin_Header_Straight_1x06_Pitch2.54mm
J_TO_FB1: Conn_01x06_Female; Pin_Header_Straight_1x06_Pitch2.54mm
Q1, Q2, Q3: BC547; TO-92_Inline_Narrow_Oval
Q4: BC557; TO-92_Inline_Narrow_Oval
Q5, Q6, Q7: MPF102; TO-92_Inline_Narrow_Oval
R1, R3, R11, R12, R13, R16, R23, R25, R26, R27, R29, R53, R56: 100K; R_Axial_DIN0207_L6.3mm_D2.5mm_P7.62mm_Horizontal
R2, R14, R19, R21, R24, R45, R46, R49, R51, R54, R55, R60: 10K; R_Axial_DIN0207_L6.3mm_D2.5mm_P7.62mm_Horizontal
R4, R5, R6, R7, R8, R22, R38: 1K; R_Axial_DIN0207_L6.3mm_D2.5mm_P7.62mm_Horizontal
R9, R10, R59: 27K; R_Axial_DIN0207_L6.3mm_D2.5mm_P7.62mm_Horizontal
R15, R18, R33: 2K; R_Axial_DIN0207_L6.3mm_D2.5mm_P7.62mm_Horizontal
R17: 3M; R_Axial_DIN0207_L6.3mm_D2.5mm_P7.62mm_Horizontal
R20, R58: 4.7M; R_Axial_DIN0207_L6.3mm_D2.5mm_P7.62mm_Horizontal
R28: 39K; R_Axial_DIN0207_L6.3mm_D2.5mm_P7.62mm_Horizontal
R30: 120K; R_Axial_DIN0207_L6.3mm_D2.5mm_P7.62mm_Horizontal
R31: 270K; R_Axial_DIN0207_L6.3mm_D2.5mm_P7.62mm_Horizontal
R32: 110K; R_Axial_DIN0207_L6.3mm_D2.5mm_P7.62mm_Horizontal
R34: 180K; R_Axial_DIN0207_L6.3mm_D2.5mm_P7.62mm_Horizontal
R35: 680K; R_Axial_DIN0207_L6.3mm_D2.5mm_P7.62mm_Horizontal
R36: 2M; R_Axial_DIN0207_L6.3mm_D2.5mm_P7.62mm_Horizontal
R37: 4.7K; R_Axial_DIN0207_L6.3mm_D2.5mm_P7.62mm_Horizontal
R39, R41: 20K; R_Axial_DIN0207_L6.3mm_D2.5mm_P7.62mm_Horizontal
R40, R42, R52: 47K; R_Axial_DIN0207_L6.3mm_D2.5mm_P7.62mm_Horizontal
R43, R44: 30K; R_Axial_DIN0207_L6.3mm_D2.5mm_P7.62mm_Horizontal
R47, R48: 15K; R_Axial_DIN0207_L6.3mm_D2.5mm_P7.62mm_Horizontal
R50: 9.1K; R_Axial_DIN0207_L6.3mm_D2.5mm_P7.62mm_Horizontal
R57: 1M; R_Axial_DIN0207_L6.3mm_D2.5mm_P7.62mm_Horizontal
RV1: 100K; Potentiometer_Trimmer_Bourns_3296W
RV2: 2K; Potentiometer_Trimmer_Bourns_3296W
SQR_PW1: 100K; Potentiometer_Alps_RK09K_Horizontal
U1, U3, U4: TL074; DIP-14_W7.62mm_Socket
U2: LM13700; DIP-16_W7.62mm_Socket
screw: MountingHole_3.2mm_M3
screw#2, screw#3, screw#4: MountingHole_3.2mm_M3

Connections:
+12V: J_PWR_IN1.1, J_PWR_TO_FB1.1, R25.2, R35.2, R36.2, R47.2, U1.4, U2.11, U3.4, U4.4
/LFO back board/-12V: J_PWR_IN1.3, J_PWR_TO_FB1.3, R20.1, R37.1, R48.1, U1.11, U2.6, U3.11, U4.11
/LFO back board/GND: J_PWR_IN1.2, J_PWR_TO_FB1.2, Q3.2, Q4.3, R22.1, R23.1, R24.1, R33.1, R34.1, R51.1, R52.2, R57.2, U1.3, U1.5, U1.12, U2.4, U2.13, U3.2, U3.5, U3.10, U4.3, U4.10
/LFO back board/Integrator/BIAS_INPUT: R21.1, U2.1
/LFO back board/Integrator/SQR_RAW: C3.1, D1.1, D2.2, R31.1, R40.2, R43.2, U3.1
/LFO back board/LED_RATE: J_TO_FB1.1, R42.1, R44.2, U3.8
/LFO back board/RMP: J_TO_FB1.6, R53.1, R54.2, R56.2, U3.14
/LFO back board/SAW: J_TO_FB1.5, R55.1, U4.1
/LFO back board/SIN: J_TO_FB1.2, R38.1
/LFO back board/SQR: J_TO_FB1.3, R60.1, U4.8
/LFO back board/TRI: C2.1, J_TO_FB1.4, Q5.1, Q7.2, R30.2, R32.2, R39.2, U1.14
/LFO back board/V_CF: J_FROM_FB1.1, J_FROM_FB1.2, J_FROM_FB1.4, R18.2, U1.2
/LFO back board/V_CV_PW: J_FROM_FB1.3, J_FROM_FB1.5, R57.1, U4.6
/LFO back board/V_SYNC: J_FROM_FB1.6, R23.2, U1.10
/LFO front board/+12V_FB: F_FINE1.1, J_PWR1.1, R9.1, R11.2, R15.2
/LFO front board/-12V_FB: F_FINE1.3, J_PWR1.3, R10.2, R12.2
/LFO front board/GND_FB: F_COARSE1.E, JCK_IN_CV_F1.P$3_SLEEVE, JCK_IN_CV_PW1.P$3_SLEEVE, JCK_IN_SYNC1.P$3_SLEEVE, JCK_OUT_RMP1.P$3_SLEEVE, JCK_OUT_SAW1.P$3_SLEEVE, JCK_OUT_SIN1.P$3_SLEEVE, JCK_OUT_SQR1.P$3_SLEEVE, JCK_OUT_TRI1.P$3_SLEEVE, J_PWR1.2
/LFO front board/LED_RATE_FB: J_FROM_BB1.1, R16.2
/LFO front board/RMP_FB: J_FROM_BB1.6, R8.1
/LFO front board/SAW_FB: J_FROM_BB1.5, R7.1
/LFO front board/SIN_FB: J_FROM_BB1.2, R4.1
/LFO front board/SQR_FB: J_FROM_BB1.3, R5.1
/LFO front board/TRI_FB: J_FROM_BB1.4, R6.1
/LFO front board/V_CF_FB: J_TO_BB1.1, R13.1
/LFO front board/V_CV_F_FB: J_TO_BB1.4, R1.1
/LFO front board/V_CV_PW_FB: J_TO_BB1.5, R2.1
/LFO front board/V_FF_FB: J_TO_BB1.2, R17.1
/LFO front board/V_PW_FB: J_TO_BB1.3, R14.2
/LFO front board/V_SYNC_FB: J_TO_BB1.6, R3.1
unnamed: C1.1, R19.2, U1.7
unnamed: C1.2, Q2.1, Q2.2, R18.1, R20.2, U1.1, U1.6
unnamed: C2.2, Q5.2, R28.1, U1.13
unnamed: C3.2, R30.1, R31.2, U3.3
unnamed: C4.1, R58.1, R59.2, U4.7
unnamed: C4.2, R56.1, R58.2, U4.5
unnamed: C5.1, C7.1, F1.1, J9.1, J10.1
unnamed: C5.2, C6.1, C7.2, C8.1, D3.2, D4.1, J3.3, J3.4, J3.5, J3.6, J3.7, J3.8, J9.2, J10.2
unnamed: C6.2, C8.2, F2.2, J9.3, J10.3
unnamed: D1.2, R26.1
unnamed: D2.1, R27.1
unnamed: D3.1, F1.2, J3.9, J3.10
unnamed: D4.2, F2.1, J3.1, J3.2
unnamed: F_COARSE1.1, R10.1
unnamed: F_COARSE1.2, R13.2
unnamed: F_COARSE1.3, R9.2
unnamed: F_COARSE1.B, Q1.3
unnamed: F_FINE1.2, R17.2
unnamed: JCK_IN_CV_F1.P$1_TIP, R1.2
unnamed: JCK_IN_CV_PW1.P$1_TIP, R2.2
unnamed: JCK_IN_SYNC1.P$1_TIP, R3.2
unnamed: JCK_OUT_RMP1.P$1_TIP, R8.2
unnamed: JCK_OUT_SAW1.P$1_TIP, R7.2
unnamed: JCK_OUT_SIN1.P$1_TIP, R4.2
unnamed: JCK_OUT_SQR1.P$1_TIP, R5.2
unnamed: JCK_OUT_TRI1.P$1_TIP, R6.2
unnamed: Q1.1, R15.1
unnamed: Q1.2, R16.1
unnamed: Q2.3, Q3.3, R19.1
unnamed: Q3.1, Q4.2
unnamed: Q4.1, R21.2
unnamed: Q5.3, R29.2
unnamed: Q6.1, R45.2
unnamed: Q6.2, R41.1, U3.7
unnamed: Q6.3, R43.1
unnamed: Q7.1, R46.2
unnamed: Q7.3, R44.1
unnamed: R11.1, SQR_PW1.1
unnamed: R12.1, SQR_PW1.3
unnamed: R14.1, SQR_PW1.2
unnamed: R22.2, RV1.2, U2.3
unnamed: R24.2, R25.1, U1.9
unnamed: R26.2, RV1.3
unnamed: R27.2, RV1.1
unnamed: R28.2, U2.5
unnamed: R29.1, U1.8
unnamed: R32.1, R33.2, U2.14
unnamed: R34.2, R36.1, U2.10, U2.12
unnamed: R35.1, U2.16
unnamed: R37.2, R38.2, U2.9
unnamed: R39.1, R41.2, U3.6
unnamed: R40.1, R42.2, U3.9
unnamed: R45.1, R47.1, R49.2
unnamed: R46.1, R48.2, R50.2
unnamed: R49.1, R51.2, RV2.1, U3.12
unnamed: R50.1, RV2.2, RV2.3
unnamed: R52.1, R53.2, U3.13
unnamed: R54.1, R55.2, U4.2
unnamed: R59.1, R60.2, U4.9
